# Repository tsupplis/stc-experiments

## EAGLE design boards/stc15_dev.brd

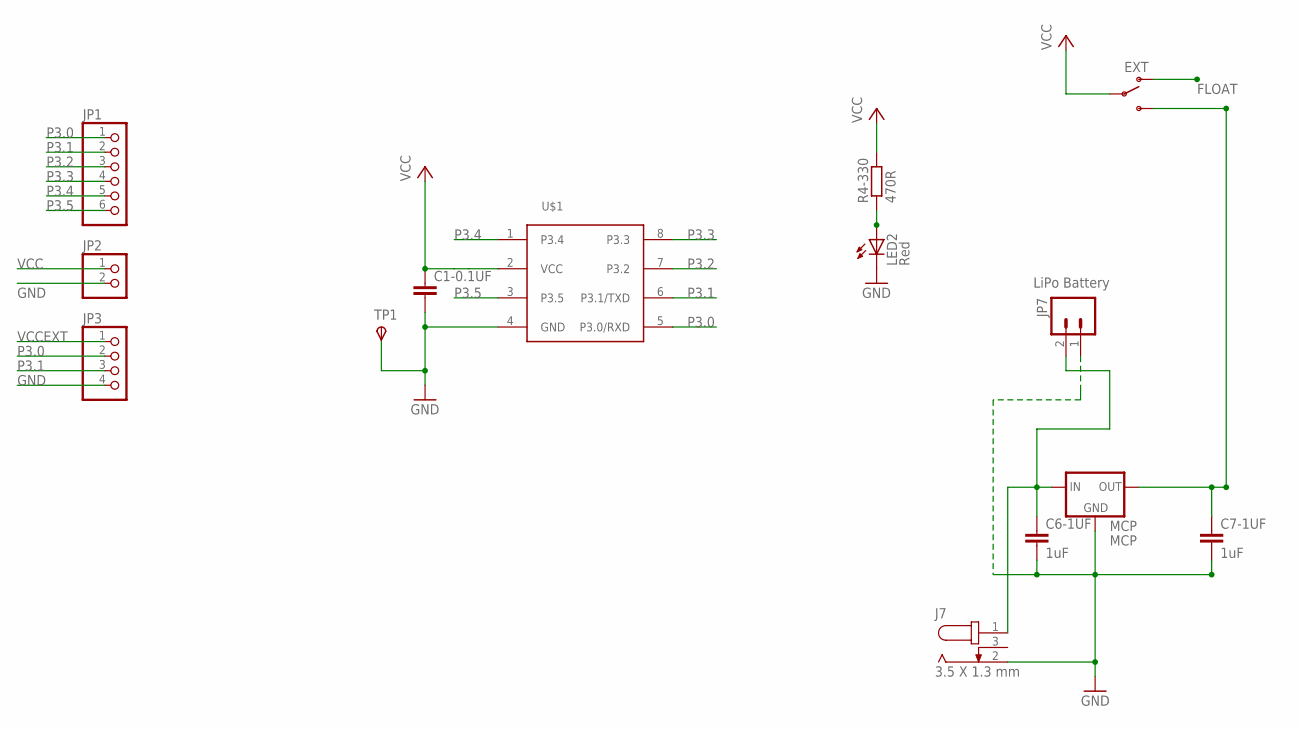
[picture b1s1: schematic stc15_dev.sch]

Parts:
C1-0.1UF: C-EU025-025X050; C025-025X050
C6-1UF, C7-1UF: 1uF; C025-025X050
J7: 3.5 X 1.3 mm; 3.5X1.3MM_DC_JACK
JP1: PINHD-1X6; 1X06
JP2: PINHD-1X2; 1X02
JP3: PINHD-1X4; 1X04
JP7: LiPo Battery; JST-2-PTH
LED2: Red; LED3MM
MCP: MCP; TO92-
ON: EXT; SWITCH-SPDT
R4-330: 470R; 0204/7
TP1: TPSTP20R; TP20R
U$1: STC15F/L10XDIP; DIL4

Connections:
FLOAT: ON.1 (O)
GND: C1-0.1UF.2, C6-1UF.2, C7-1UF.2, J7.2, JP2.2, JP3.4, JP7.1, LED2.K (C), MCP.3 (GND), TP1.TP, U$1.4 (GND)
unnamed: LED2.A, R4-330.1
P3.0: JP1.1, JP3.2, U$1.5 (P3.0/RXD)
P3.1: JP1.2, JP3.3, U$1.6 (P3.1/TXD)
P3.2: JP1.3, U$1.7 (P3.2)
P3.3: JP1.4, U$1.8 (P3.3)
P3.4: JP1.5, U$1.1 (P3.4)
P3.5: JP1.6, U$1.3 (P3.5)
VCC: C1-0.1UF.1, JP2.1, ON.2, R4-330.2, U$1.2 (VCC)
VCCEXT: C6-1UF.1, J7.1, JP3.1, JP7.2, MCP.2 (IN)
VCCREG: C7-1UF.1, MCP.1 (OUT), ON.3 (S)

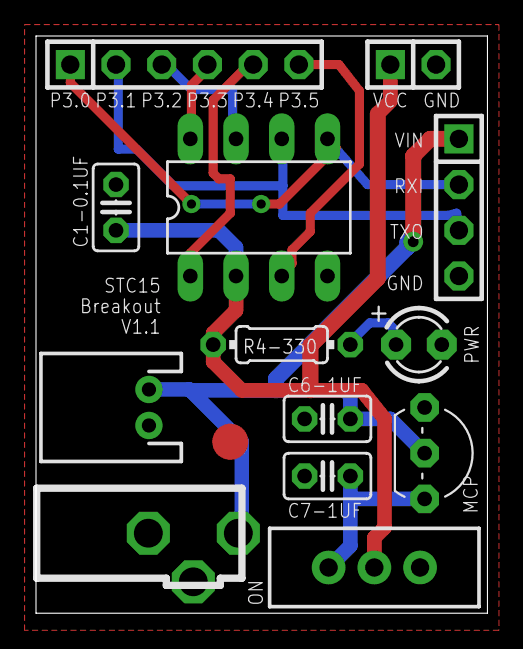
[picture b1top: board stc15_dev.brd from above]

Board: 2 copper layers, 25.1 x 32.1 mm, 14 parts (0 on the bottom side), 11 nets.

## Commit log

2016-04-05 Initial Content

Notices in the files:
parts and their libraries:
SparkFun: Licensing: CC v3.0 Share-Alike You are welcome to use this library for commercial purposes.
